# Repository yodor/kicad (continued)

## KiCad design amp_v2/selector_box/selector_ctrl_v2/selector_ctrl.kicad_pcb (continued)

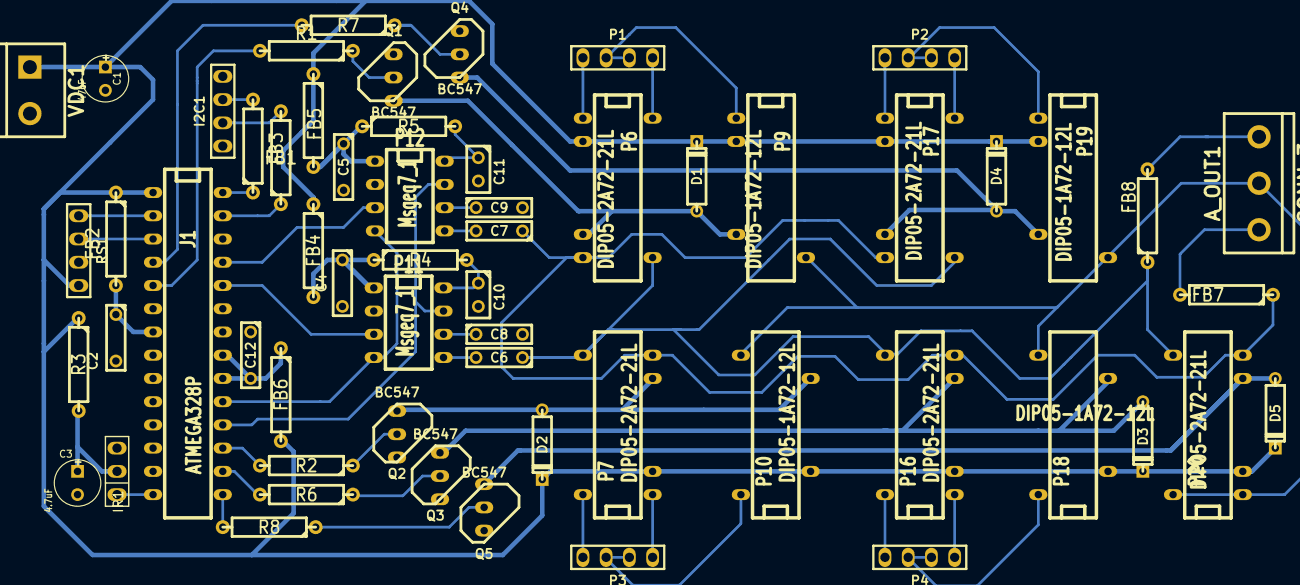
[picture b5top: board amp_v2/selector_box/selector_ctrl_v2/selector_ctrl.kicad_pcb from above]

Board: 2 copper layers, 59 parts (0 on the bottom side), 56 nets.

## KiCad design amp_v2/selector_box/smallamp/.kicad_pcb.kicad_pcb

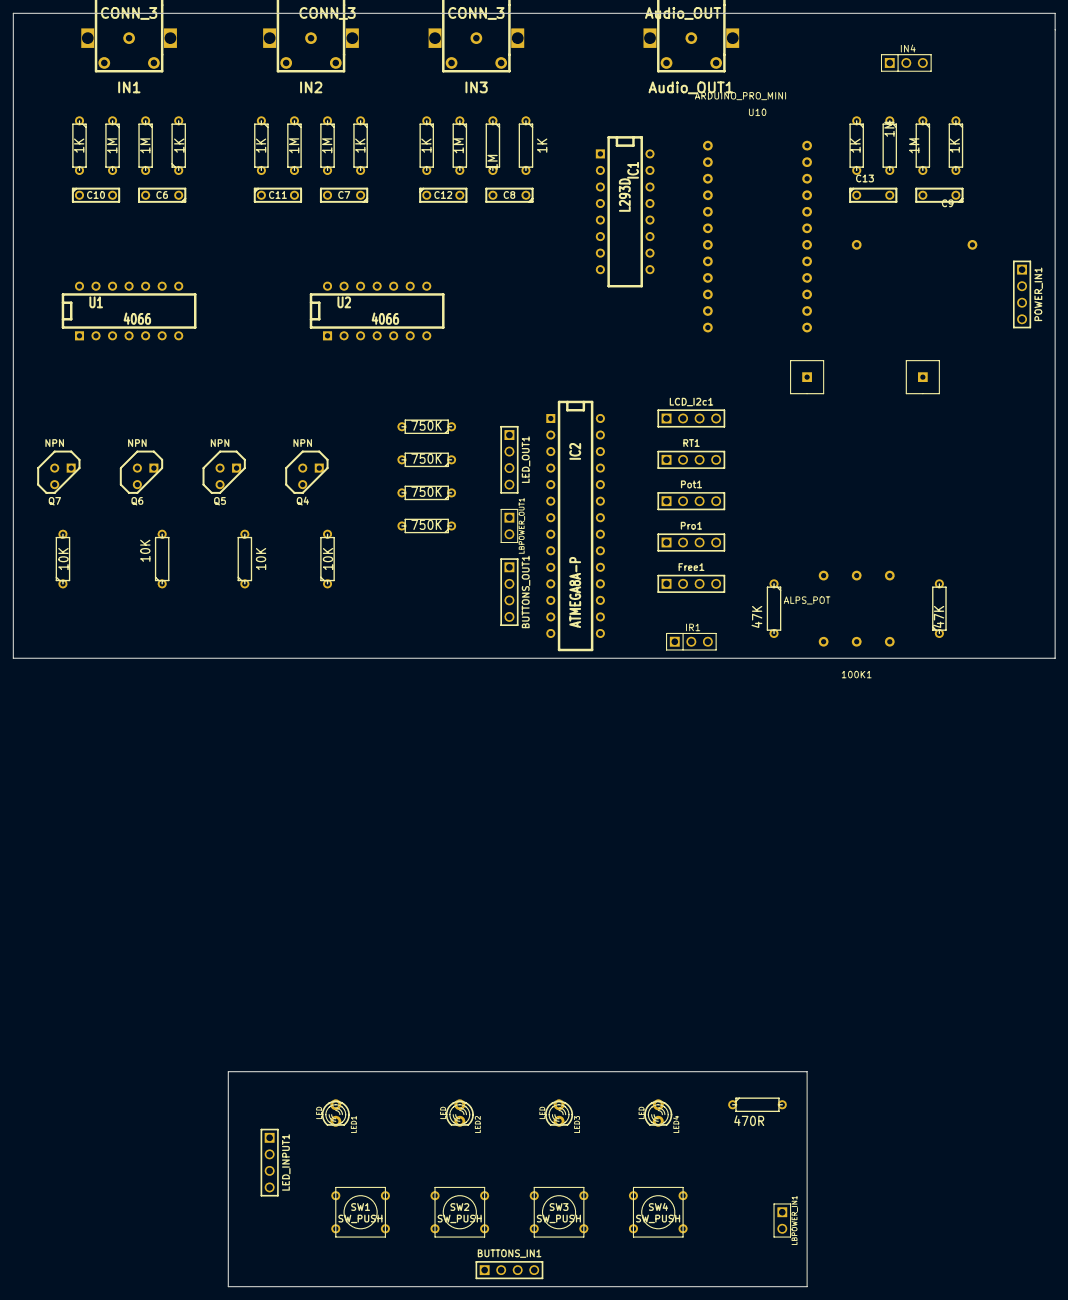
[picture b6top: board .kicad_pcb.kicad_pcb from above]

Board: 2 copper layers, 160.0 x 99.1 mm, 71 parts (0 on the bottom side), 67 nets, no tracks yet.

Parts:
100K1: ALPS_POT; ALPS Motorized
Audio_OUT1: Audio_OUT; RCA_my
BUTTONS_IN1: BUTTONS_IN; PIN_ARRAY_4x1
BUTTONS_OUT1: BUTTONS_OUT; PIN_ARRAY_4x1
C6, C7, C8, C9, C10, C11, C12, C13: 100n; C2
Free1: CONN_4; PIN_ARRAY_4x1
IC1: L293D; DIP-16__300
IC2: ATMEGA8A-P; DIP-28__300
IN1, IN2, IN3: CONN_3; RCA_my
IN4: CONN_3; PIN_ARRAY_3X1
IR1: CONN_3; PIN_ARRAY_3X1
LBPOWER_IN1: LB_POWERIN; PIN_ARRAY_2X1
LBPOWER_OUT1: LBPOWER_OUT; PIN_ARRAY_2X1
LCD_I2c1: LCD_OUT; PIN_ARRAY_4x1
LED1, LED2, LED3, LED4: LED; LED-3MM
LED_INPUT1: LED_INPUT; PIN_ARRAY_4x1
LED_OUT1: LED_OUT; PIN_ARRAY_4x1
POWER_IN1: POWER_IN; PIN_ARRAY_4x1
Pot1: CONN_4; PIN_ARRAY_4x1
Pro1: CONN_4; PIN_ARRAY_4x1
Q4, Q5, Q6, Q7: NPN; TO92-123
R9: 470R; R3
R10, R11, R12, R13: 750K; R3
R14, R15, R16, R17, R18, R19, R20, R21: 1K; R3
R22, R23, R24, R25, R30, R31, R32, R33: 1M; R3
R26, R27, R28, R29: 10K; R3
R34, R35: 47K; R3
RT1: CONN_4; PIN_ARRAY_4x1
SW1, SW2, SW3, SW4: SW_PUSH; SW_PUSH_SMALL
U1, U2: 4066; DIP-14__300
U10: ARDUINO_PRO_MINI; Arduino Pro MINI

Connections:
5.6V: POWER_IN1.3, R26.1, R27.1, R28.1, R29.1, U1.14, U2.14
5V: Free1.1, IC1.8, IC2.7, IR1.1, LBPOWER_OUT1.1, LCD_I2c1.1, POWER_IN1.1, Pot1.1, Pro1.1, RT1.1, U10.24
Audio GND: 100K1.3, 100K1.6, Audio_OUT1.1, IN1.1, IN2.1, IN3.1, IN4.1, POWER_IN1.4, R22.1, R23.1, R24.1, R25.1, R30.1, R31.1, R32.1, R33.1, R34.1, R35.1
Audio Output L: 100K1.2, Audio_OUT1.3
Audio Output R: 100K1.5, Audio_OUT1.2
CH1E: IC2.2, LED_OUT1.1, R10.1
CH2E: IC2.3, LED_OUT1.2, R11.1
CH3E: IC2.4, LED_OUT1.3, R12.1
CH4E: IC2.5, LED_OUT1.4, R13.1
GND: Free1.4, IC1.12, IC1.13, IC2.8, IR1.2, LBPOWER_OUT1.2, LCD_I2c1.4, POWER_IN1.2, Pot1.4, Pro1.4, Q4.1, Q5.1, Q6.1, Q7.1, RT1.4, U1.7, U2.7, U10.23
Motor_L: 100K1.7, IC1.14
Motor_R: 100K1.8, IC1.11
unnamed: BUTTONS_OUT1.1, IC2.6
unnamed: BUTTONS_OUT1.2, IC2.11
unnamed: BUTTONS_OUT1.3, IC2.12
unnamed: BUTTONS_OUT1.4, IC2.13
unnamed: IR1.3, U10.5
unnamed: Q7.3, R29.2, U1.12, U2.12
unnamed: LBPOWER_IN1.1, R9.2
unnamed: BUTTONS_IN1.4, SW4.1
unnamed: LED4.2, LED_INPUT1.4
unnamed: BUTTONS_IN1.1, SW1.1
unnamed: BUTTONS_IN1.2, SW2.1
unnamed: BUTTONS_IN1.3, SW3.1
unnamed: Q4.2, R10.2
unnamed: Q5.2, R11.2
unnamed: Q7.2, R13.2
unnamed: IC1.9, U10.8
unnamed: IC1.15, U10.6
unnamed: IC1.10, U10.7
unnamed: LED1.2, LED_INPUT1.1
unnamed: LED2.2, LED_INPUT1.2
unnamed: LED3.2, LED_INPUT1.3
unnamed: LBPOWER_IN1.2, SW1.2, SW2.2, SW3.2, SW4.2
unnamed: LED1.1, LED2.1, LED3.1, LED4.1, R9.1
unnamed: Q6.2, R12.2
unnamed: C13.2, R33.2, U2.11
unnamed: IN1.3, R14.2
unnamed: IN2.3, R15.1
unnamed: IN3.3, R16.1
unnamed: C6.1, R14.1
unnamed: Q4.3, R26.2, U1.13, U2.13
unnamed: Q6.3, R28.2, U1.6, U2.6
unnamed: Q5.3, R27.2, U1.5, U2.5
unnamed: C10.2, R30.2, U2.1
unnamed: C8.1, R16.2
unnamed: C8.2, R24.2, U1.8
unnamed: C12.1, R20.2
unnamed: C12.2, R32.2, U2.8
unnamed: C9.1, R17.2
unnamed: C9.2, R25.2, U1.11
unnamed: C13.1, R21.2
unnamed: C6.2, R22.2, U1.1
unnamed: C11.2, R31.2, U2.4
unnamed: C7.2, R23.2, U1.4
unnamed: IN1.2, R18.1
unnamed: C7.1, R15.2
unnamed: IN3.2, R20.1
unnamed: IN4.2, R21.1
unnamed: IN4.3, R17.1
unnamed: C10.1, R18.2
unnamed: IN2.2, R19.1
unnamed: C11.1, R19.2
SCL: Free1.3, IC2.28, LCD_I2c1.3, Pot1.3, Pro1.3, RT1.3
SDA: Free1.2, IC2.27, LCD_I2c1.2, Pot1.2, Pro1.2, RT1.2
Selector Output L: 100K1.1, R34.2, U1.2, U1.3, U1.9, U1.10
Selector Output R: 100K1.4, R35.2, U2.2, U2.3, U2.9, U2.10

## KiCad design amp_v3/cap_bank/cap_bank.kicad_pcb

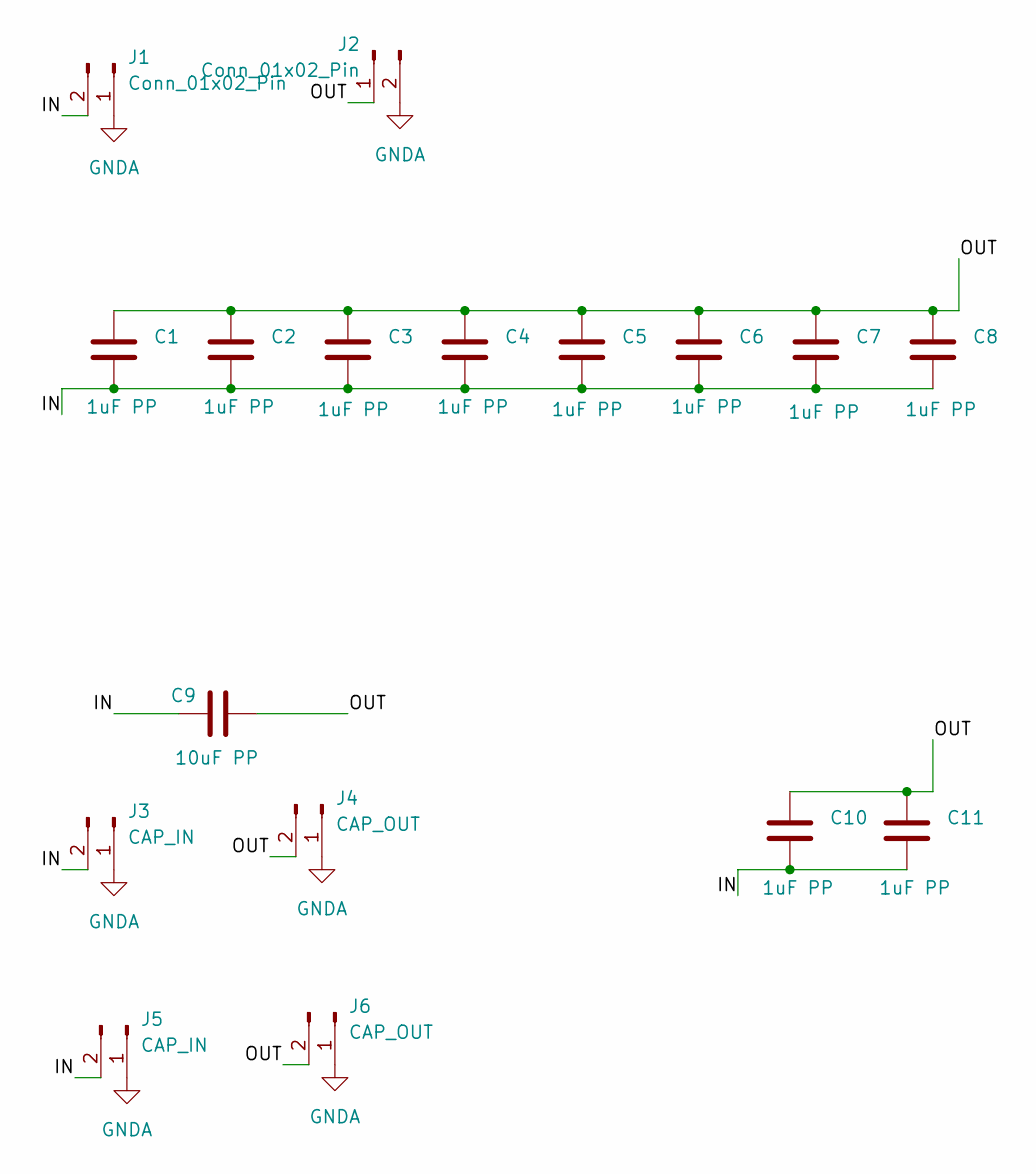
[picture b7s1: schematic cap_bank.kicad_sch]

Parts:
C1, C2, C3, C4, C5, C6, C7, C8, C10, C11: 1uF PP; JFC
C9: 10uF PP; 10uF - D18 - W46
J1, J2: Conn_01x02_Pin; JST_XH_B2B-XH-A_1x02_P2.50mm_Vertical
J3, J5: CAP_IN; JST_XH_B2B-XH-A_1x02_P2.50mm_Vertical
J4, J6: CAP_OUT; JST_XH_B2B-XH-A_1x02_P2.50mm_Vertical

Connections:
/IN: C1.2, C2.2, C3.2, C4.2, C5.2, C6.2, C7.2, C8.2, C9.1, C10.2, C11.2, J1.2, J3.2, J5.2
/OUT: C1.1, C2.1, C3.1, C4.1, C5.1, C6.1, C7.1, C8.1, C9.2, C10.1, C11.1, J2.1, J4.2, J6.2
GNDA: J1.1, J2.2, J3.1, J4.1, J5.1, J6.1

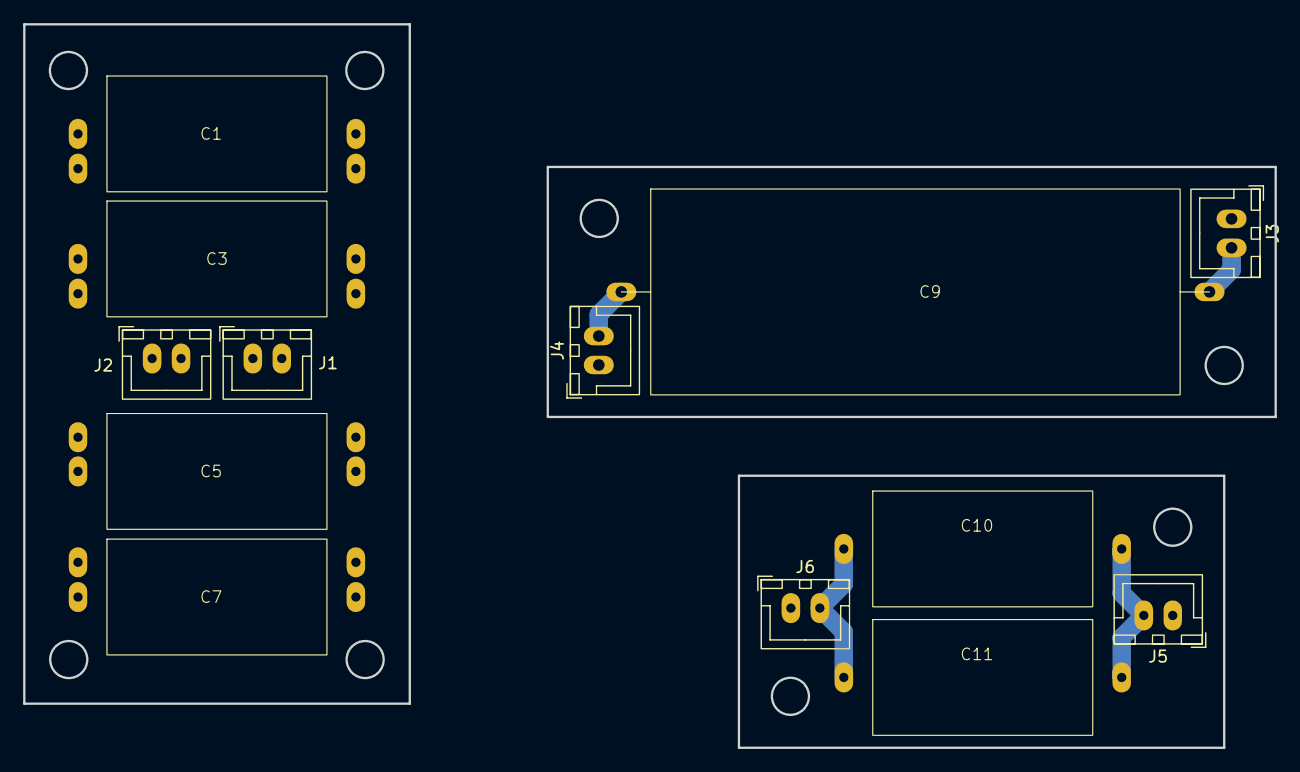
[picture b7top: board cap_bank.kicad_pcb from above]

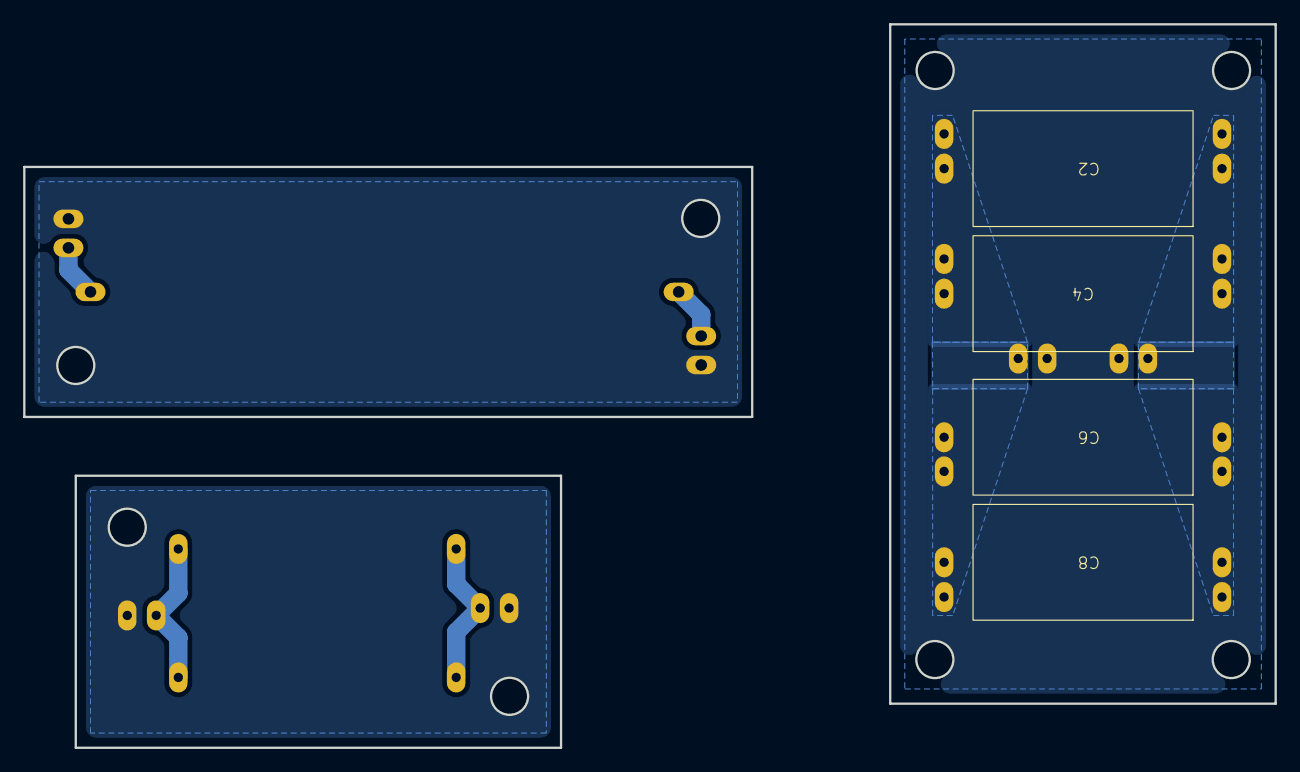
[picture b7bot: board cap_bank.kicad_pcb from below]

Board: 2 copper layers, 108.1 x 62.5 mm, 17 parts (4 on the bottom side), 3 nets.

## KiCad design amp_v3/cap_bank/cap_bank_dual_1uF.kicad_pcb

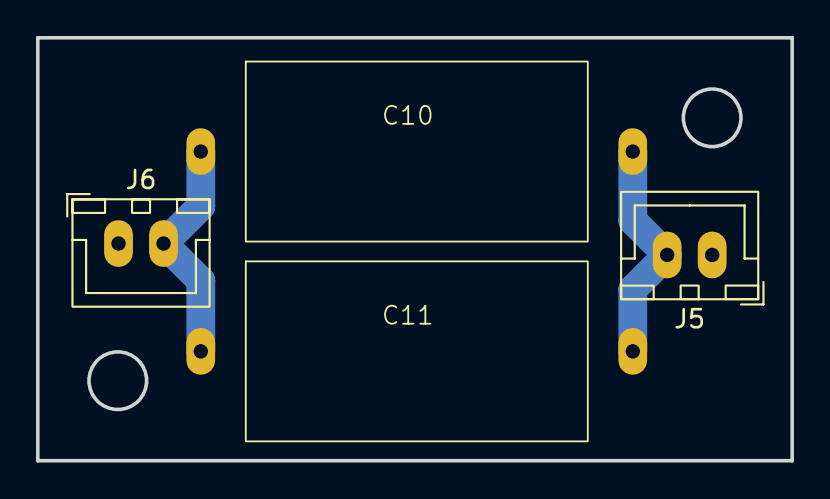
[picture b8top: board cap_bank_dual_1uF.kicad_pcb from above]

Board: 2 copper layers, 41.9 x 23.5 mm, 4 parts (0 on the bottom side), 3 nets.

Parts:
C10, C11: 1uF PP; JFC
J5: CAP_IN; JST_XH_B2B-XH-A_1x02_P2.50mm_Vertical
J6: CAP_OUT; JST_XH_B2B-XH-A_1x02_P2.50mm_Vertical

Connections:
/IN: C10.2, C11.2, J5.2
/OUT: C10.1, C11.1, J6.2
GNDA: J5.1, J6.1
